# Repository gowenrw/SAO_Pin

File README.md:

# SAO_Pin

This is where all the files for SAO_Pin will be stored.

This includes code and art and cad and fab files.  All the things.

## File Structure

This is the file structure of this repository

* [/](/README.md) - YOU ARE HERE
* [/art/](./art/) - Artwork and other graphics created by this project
  * [/art/inspiration/](./art/inspiration/) - Art and graphics pulled from other sources used as inspiration for this project
  * [/art/fonts/](./art/fonts/) - Fonts used in art and graphics
* [/code/](./code/) - All project related Code / Firmware
* [/docs/](./docs/) - Documentation created by this project including web pages
* [/eda/](./eda/) - Electronic Design Automation files (i.e. KiCad)
  * [/eda/SAO_Pin/](./eda/SAO_Pin/) - KiCad 9.x project folder for the SAO_Pin PCB
* [/reference_parts/](./reference_parts/) - Submodule of Third Party Documentation related to components
* [./README.md](/README.md) - This File
* [./LICENSE](/LICENSE) - Currently set to MIT

Note: the reference_parts directory is a link to a submodule repository.
To add it use the following cmd after cloning this:
```
git submodule add https://github.com/gowenrw/reference_parts reference_parts
```
This will make a link to the current commit of that repo.
To update it to a newer commit after its been added use this cmd:
```
git submodule update --init --recursive
```

## Project Details

The SAO_Pin is a simple adapter that will allow you to wear any badge Shitty Add On (SAO) as a broach pin instead of being attached to a badge or a totem.

The PCB is small at 25mm x 40mm, just large enough to hold its few components and hopefully small enough to be hidden behind any attached SAO.

The Gerber files have been made available [HERE](https://github.com/gowenrw/SAO_Pin/raw/refs/heads/master/eda/SAO_Pin/gerber/2025-06-03.zip) for anyone to use to order thier own PCBs.

Simply download the [ZIP file](https://github.com/gowenrw/SAO_Pin/raw/refs/heads/master/eda/SAO_Pin/gerber/2025-06-03.zip) and then choose your PCB manufacture to upload it to for ordering.

The design is simple, requiring only five components:

* SAO 2x3 keyed socket header, the type used on badges not the type used on SAO's.
  * 
* CR2032 Battery Holder with THT pins
  * 
* 20mm Brooch clip pin clasp with M2 sized screw holes for attachment
  * 
* M2 screws for attaching the pin.
  * 
* M2 nuts for attaching the pin.
  * 

Here are some links for ordering the components:

* SAO 2x3 keyed socket header, the type used on badges not the type used on SAO's.
  * https://www.aliexpress.us/item/2251832874579437.html
  * https://www.ebay.com/itm/173960769032

* CR2032 Battery Holder with THT pins
  * https://www.aliexpress.us/item/3256806213778380.html
  * https://www.amazon.com/dp/B07T3WP9T4

* 20mm Brooch clip pin clasp with M2 sized screw holes for attachment
  * https://www.aliexpress.us/item/2255800106050402.html - Choose the 2cm option
  * https://www.amazon.com/dp/B0BJJ4L94L - Choose the 20mm option

* M2 screws for attaching the pin.
  * https://www.aliexpress.us/item/3256808318392916.html - Choose M2 Screw 5mm Length
  * https://www.amazon.com/dp/B082XXXRV6 - Choose M2 Screw 5mm Length

* M2 nuts for attaching the pin.
  * https://www.aliexpress.us/item/3256806543218419.html - Choose M2 Nut
  * https://www.amazon.com/dp/B0CMG7Q27P - Choose M2 Nut

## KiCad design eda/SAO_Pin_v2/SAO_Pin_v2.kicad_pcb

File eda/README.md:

# Electronic Design Automation

This is where all the Electronic Design Automation files for the PCB(s) will be stored.
The EDA used is KiCad 9.x unless otherwise specified.

The KiCad projects have been configured to use local libraries for long term sustainability per the best practices listed [HERE](https://hackaday.com/2017/05/18/kicad-best-practises-library-management/) and elsewhere.

## File Structure

This is the file structure of this repository

* [/](/README.md) - Home
* [/eda](/eda/) - YOU ARE HERE
  * /eda/SAO_Pin/ - KiCad project folder for the PCB(s)
    * ./3d_models/ - This directory contains footprint 3d model files
    * ./gerber/ - This directory contains gerber formatted files for manufacturing
    * ./lib_fp/ - This directory contains footprint module directories
    * ./lib_sh/ - This directory contains schematic library files
    * ./snapshots/ - This directory contains prints of schematic / cad files and images of preview / final product

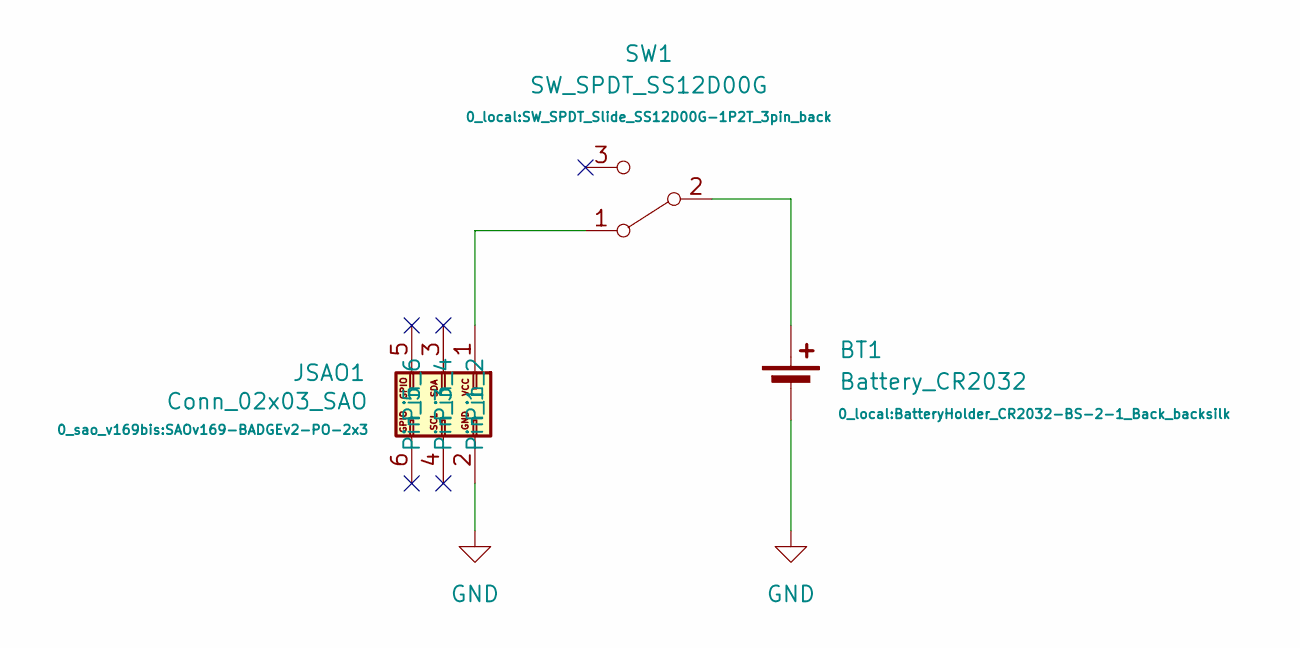
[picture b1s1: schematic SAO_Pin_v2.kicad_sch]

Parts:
BT1: Battery_CR2032; BatteryHolder_CR2032-BS-2-1_Back_backsilk
JSAO1: Conn_02x03_SAO; SAOv169-BADGEv2-PO-2x3
SW1: SW_SPDT_SS12D00G; SW_SPDT_Slide_SS12D00G-1P2T_3pin_back

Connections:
GND: BT1.2 (-), JSAO1.2
unnamed: BT1.1 (+), SW1.2 (B)
unnamed: JSAO1.1, SW1.1 (A)

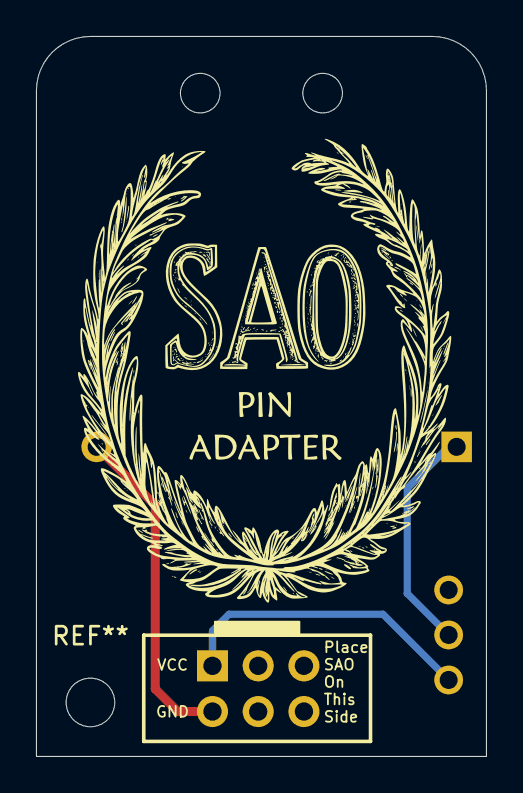
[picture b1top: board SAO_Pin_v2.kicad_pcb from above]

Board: 2 copper layers, 25.0 x 40.0 mm, 4 parts (0 on the bottom side), 3 nets.

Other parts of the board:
EdgeCuts: SAO_Pin_EdgeCuts

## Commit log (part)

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2025-02-09 Initial template updates
2025-05-23 basic 2032 cell power for SAO
2025-05-23 Added drill footnotes and gerber files
2025-05-29 pcb updates
2025-06-04 final art and gerbers
2025-06-06 documentation updates
2025-06-06 updated reference_parts submodule reference
2025-06-06 document updates
2025-08-24 proto snaps
2026-05-29 Add files via upload
    This is a 2.0 with a switch and a lanyard hole
2026-05-29 Delete eda/SAO_Pin_2.kicad_sch
    placed in wrong location
2026-05-29 Delete eda/SAO_Pin_2.kicad_pro
    Placed in wrong location
2026-05-29 Delete eda/SAO_Pin_2.kicad_pcb
    Placed in wrong location
